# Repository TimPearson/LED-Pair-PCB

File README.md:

# LED-Pair-PCB
Part of the model railway lighting project; this is a PCB design

This is a small connector board that is used to drive two LEDs - it takes a roughly 9v input (probably anywhere from 7-10v is fine) and drives two leds - note both leds need to be present for the circuit to be made. It has a signal input (which is -ve) to control if the LEDs are on or not, and a 5V pass through to connect on to the next board in a sequence of these boards.

The design is in EAGLE PCB design

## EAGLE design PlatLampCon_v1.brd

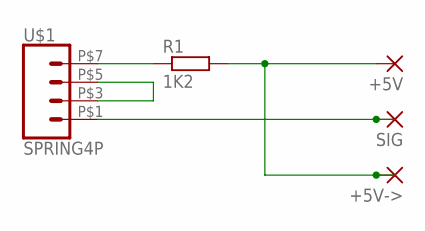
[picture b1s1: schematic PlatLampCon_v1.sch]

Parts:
+5V, +5V->: 2,15/1,0
R1: 1K2; 0207/7
SIG: 2,15/1,0
U$1: SPRING4P; SPRING-CON4P

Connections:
unnamed: +5V.1, +5V->.1, R1.2
unnamed: R1.1, U$1.P$7 (4)
unnamed: U$1.P$3 (2), U$1.P$5 (3)
unnamed: SIG.1, U$1.P$1 (1)

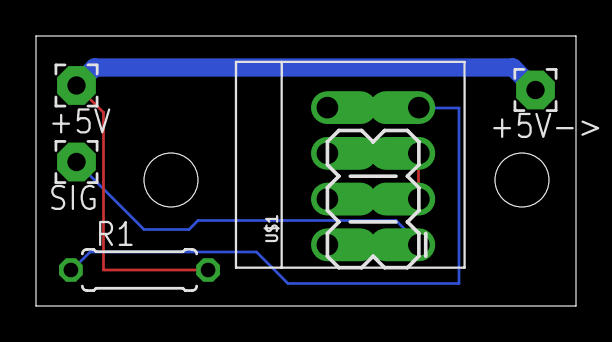
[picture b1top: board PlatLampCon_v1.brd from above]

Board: 2 copper layers, 30.0 x 15.0 mm, 5 parts (0 on the bottom side), 4 nets.
